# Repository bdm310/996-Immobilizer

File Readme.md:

# Porsche 996/986 Immobilizer
This is a repository of information about the immobilizer on these 911/Boxster/Cayman cars. Part number of the unit here is 996-618-260-05.

There are a few useful bits of information needed when working with these:
- The part number of the immobiliser is located at the beginning of the eeprom from address 0x009 to 0x00E. Checking this allows you to verify that the dump you are using is correct.
- Key fob radio code is 12 8 bit hex characters e.g. 40 01 4F 13 06 1E 41 5F 10 38 77 26. This is a unique ID and some type of initialization/sync info for programming the remote control part of the key. This comes on a tag with new keys and was potentially provided with the car's manual for the original keys. Sometimes this tag got taped to the underside of the hood. You need this to program any remote control. I haven't found a way to reverse engineer it out of a remote yet. See the appropriately named folder for initial efforts.
- Transponder code is a unique ID on the RFID pill in the key head. You can probably re-use these transponders with special tools. They're cheap as of 2023 though, so it's probably not worth getting tools or investing time to reverse engineering them. Most should be an ID48 transponder chip commonly used across a lot of manufacturers and models. I got a set of 4 for $10 from Amazon, UPC 712288935256.
- Key learning code is 3 8 bit hex characters e.g. 4C 02 E3. This is needed to program transponders and remote controls. This code is at the end of EEPROM memory, at 0x1F7 and 0x1EE.
- Immobilizer code is needed for programming new/used modules to different cars. This is probably somewhere in the EEPROM too but I haven't needed to find it yet.

Using PIWIS to try various key learning codes:
 - Response to key input from 0x025 - 29000 - 7F 27 35 - key out of order
 - Response to key input from 0x1ee - 29000 - 7F 27 33 - No access right!
 - Got no access right again on key from 0x025

So, you can get the learning code wrong at least 3 times with no lockout. Though, I am now noticing that the second attempt above actually had the right key and gave a different error than the first, definitely wrong, key attempt. Thus, there may be some time delay after a wrong attempt but thankfully no hard lockout.

## Immobilizer versions
The M534 and M535 are the same module but with 433MHz and 315MHz (USA) antennas for the keyfob, respectively.

There are at least two major versions of the M534/M535 module. The early cars use part 996.618.260.0x (where x varies according to minor revision) and the later cars use 996.618.262.0x. For boxsters, the changeover happend in 2001, when the electronic frunk release was implemented. There are a number of [wiring differences](<./M53x wiring differences.md>) between the major revisions which make them non-interchangable. It may be possible to repin certain wires to get basic functionaly, but I have not found anyone who tried this. 

## EEPROM
There's a 93LC66 EEPROM right next to the main processor. The processor has only ROM, so this EEPROM is the only possible place for configuration and state memory. Conveniently, this means you can easily clone a module or inspect the memory contents. I had no issues using an SOIC-8 chip clip and TL866 programmer in-circuit without removing the EEPROM or lifting any leads. If you intend to do any experimentation, it would be prudent to read out this chip beforehand. Since it's the only non-volatile memory, it seems safe to perform any PIWIS or other action while experimenting so long as you have a backup.

If you've got a water damaged module, you can probably get a cheap junkyard replacement and clone. That is, in fact, what started all this.

The ods spreadsheet details what I've learned about the detailed contents of this chip. There's a couple binary dumps here as well.

## Firmware
This module uses an M37710 microcontroller. Turns out that it looks just like an M5M27C101K when wired up a certain way, the M7700 folder has a PCB that does the right stuff. The binary hopefully will give up some secrets for programming key remotes without the original tags.

## Key Fob Radio Code
Every key head I've seen so far uses a Microchip product. I suspect the cipher is Keeloq but I cannot match the transmitted bitstream to any product datasheet I can find. Most notably, it's missing the seemingly ubiquitous synchronization preamble. You'll find LogicPro raw captures and a PulseView composite of a few captures in the reverse engineering folder.

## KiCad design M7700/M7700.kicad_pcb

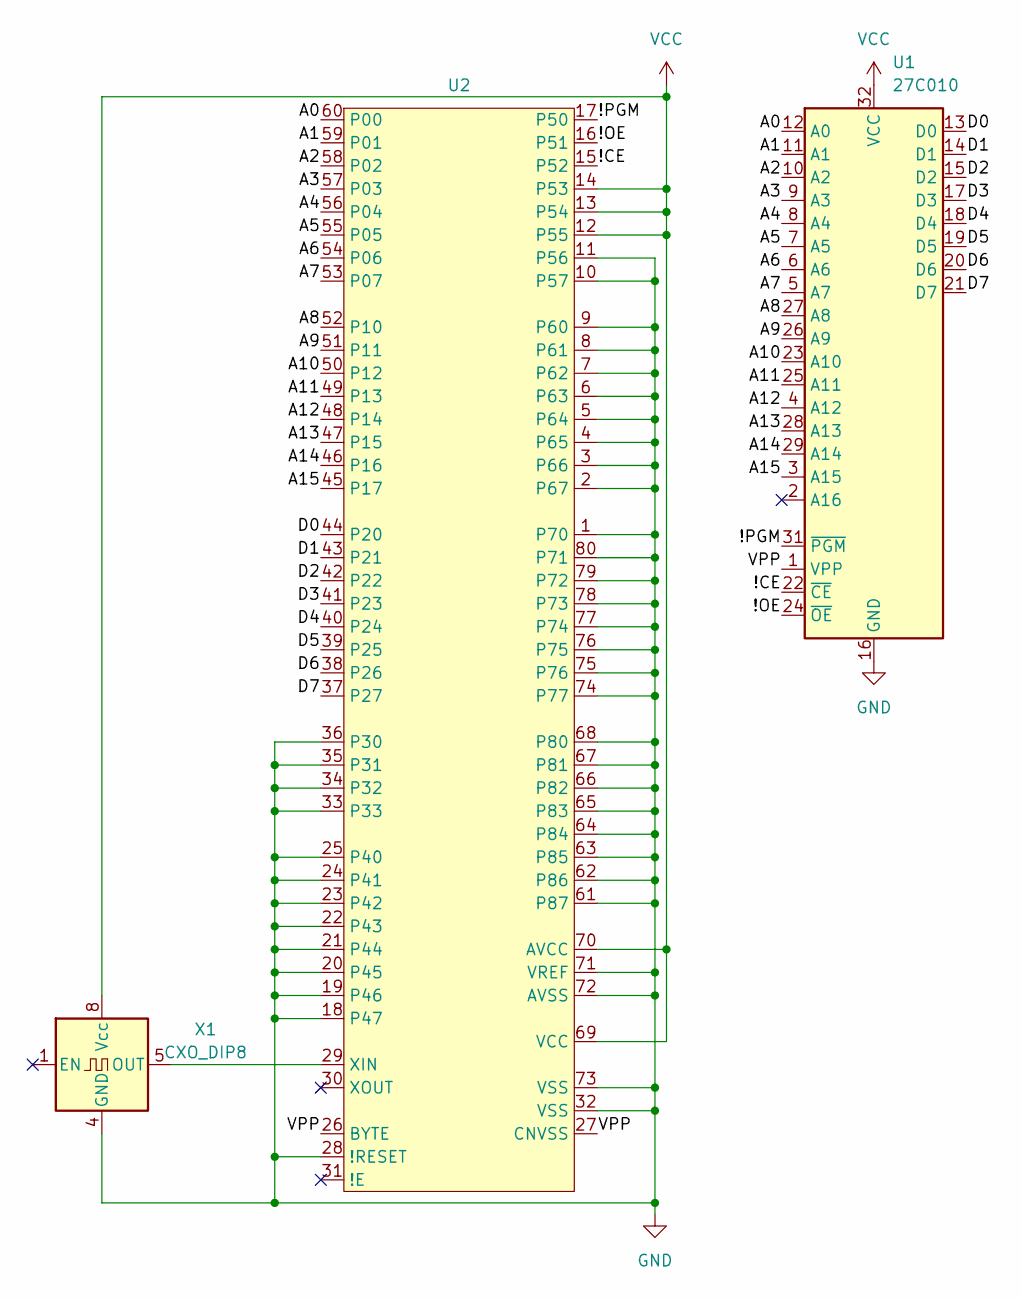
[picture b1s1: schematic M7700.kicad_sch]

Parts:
U1: 27C010; DIP-32_W7.62mm
U2: QFP080-P-1420
X1: CXO_DIP8; Oscillator_DIP-8

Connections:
/!CE: U1.22 (~CE), U2.15 (P52)
/!OE: U1.24 (~OE), U2.16 (P51)
/!PGM: U1.31 (~PGM), U2.17 (P50)
/A0: U1.12 (A0), U2.60 (P00)
/A1: U1.11 (A1), U2.59 (P01)
/A2: U1.10 (A2), U2.58 (P02)
/A3: U1.9 (A3), U2.57 (P03)
/A4: U1.8 (A4), U2.56 (P04)
/A5: U1.7 (A5), U2.55 (P05)
/A6: U1.6 (A6), U2.54 (P06)
/A7: U1.5 (A7), U2.53 (P07)
/A8: U1.27 (A8), U2.52 (P10)
/A9: U1.26 (A9), U2.51 (P11)
/A10: U1.23 (A10), U2.50 (P12)
/A11: U1.25 (A11), U2.49 (P13)
/A12: U1.4 (A12), U2.48 (P14)
/A13: U1.28 (A13), U2.47 (P15)
/A14: U1.29 (A14), U2.46 (P16)
/A15: U1.3 (A15), U2.45 (P17)
/D0: U1.13 (D0), U2.44 (P20)
/D1: U1.14 (D1), U2.43 (P21)
/D2: U1.15 (D2), U2.42 (P22)
/D3: U1.17 (D3), U2.41 (P23)
/D4: U1.18 (D4), U2.40 (P24)
/D5: U1.19 (D5), U2.39 (P25)
/D6: U1.20 (D6), U2.38 (P26)
/D7: U1.21 (D7), U2.37 (P27)
/VPP: U1.1 (VPP), U2.26 (BYTE), U2.27 (CNVSS)
GND: U1.16 (GND), U2.1 (P70), U2.2 (P67), U2.3 (P66), U2.4 (P65), U2.5 (P64), U2.6 (P63), U2.7 (P62), U2.8 (P61), U2.9 (P60), U2.10 (P57), U2.11 (P56), U2.18 (P47), U2.19 (P46), U2.20 (P45), U2.21 (P44), U2.22 (P43), U2.23 (P42), U2.24 (P41), U2.25 (P40), U2.28 (!RESET), U2.32 (VSS), U2.33, U2.34 (P32), U2.35 (P31), U2.36 (P30), U2.61 (P87), U2.62 (P86), U2.63 (P85), U2.64 (P84), U2.65 (P83), U2.66 (P82), U2.67 (P81), U2.68 (P80), U2.71 (VREF), U2.72 (AVSS), U2.73 (VSS), U2.74 (P77), U2.75 (P76), U2.76 (P75), U2.77 (P74), U2.78 (P73), U2.79 (P72), U2.80 (P71), X1.4 (GND)
unnamed: U2.29 (XIN), X1.5 (OUT)
VCC: U1.32 (VCC), U2.12 (P55), U2.13 (P54), U2.14 (P53), U2.69 (VCC), U2.70 (AVCC), X1.8 (Vcc)

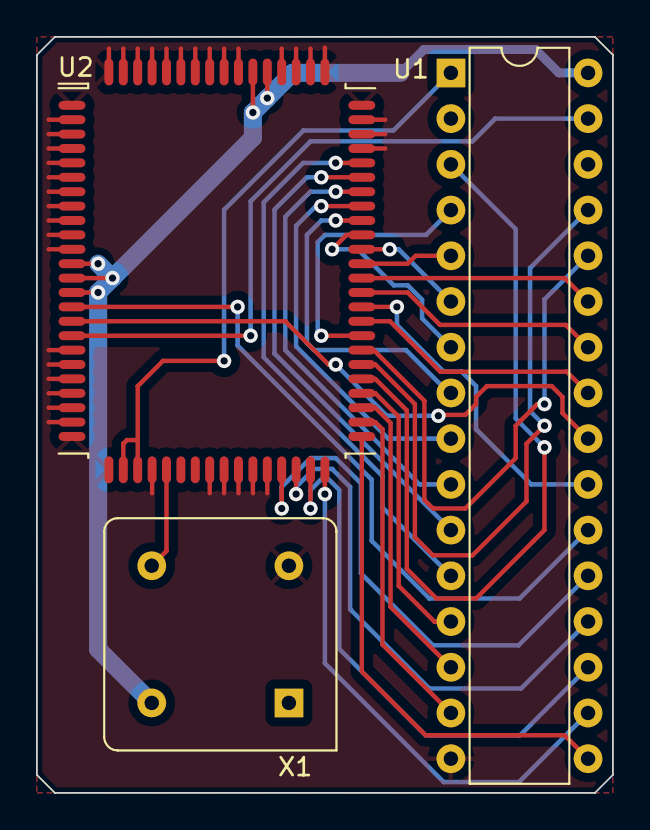
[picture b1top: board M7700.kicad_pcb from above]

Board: 2 copper layers, 32.0 x 42.0 mm, 3 parts (0 on the bottom side), 31 nets.

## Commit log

2025-04-22 add information
2025-04-22 edit for clarity. radio code could refer to pin code for the stereo system
2025-04-22 update table layout
2025-05-30 Add transponder information
